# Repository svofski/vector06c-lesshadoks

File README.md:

ЛЕШАДОК ПОМПЕ
=============

ЛЕШАДОК ПОМПЕ (Les shadoks pompaient) is an expansion board for Вектор-06ц home computer from USSR era.

Features (real and planned):
  - [x] RAM disk expansion in SDRAM
  - [x] AY and other sound device emulation
  - [x] Joystick ports
  - [x] floppy disk emulator
  - [x] floppy images on SD card
  - [ ] floppy images downloaded from the internets
  - [x] ESP12F working as FPGA configurator
  - [x] ESP12F as user interface for SD card image selection
  - [ ] ESP12F for uploading floppy disk images to SDRAM
  - [ ] VI53 sound passthrough
  
Key hardware features:
  * Main chip: EP4CE6 Intel Cyclone IV device
  * 8MB SDRAM (working at 96MHz)
  * ESP12F module
  * Audio output with amplifier
  * Analog input for internal audio mixing (using LVDS sigma-delta ADC)

Board schematic
---------------
[Schematic](/kicad/shadok-cheap/shadok.pdf) (pdf)

Build instructions
------------------
This project consists of many parts and putting it together is not a simple task.
Here I wrote down some instructions primarily for myself to be able to remember
what to do. Good luck!

### PART 1 Building Cosmogol999 (esp8266 firmware)

1. Get the sources
```
git clone --recurse-submodules https://github.com/svofski/vector06c-lesshadoks
```

2. Prepare esp-open-sdk
Follow instructions at https://github.com/pfalcon/esp-open-sdk.
Mind the requirements, then get the SDK and build:
```
git clone --recursive --depth=1 https://github.com/pfalcon/esp-open-sdk.git
cd esp-open-sdk
make STANDALONE=y
```

After the toolchain is ready, do as it says:
```
export PATH=$HOME/esp-open-sdk/xtensa-lx106-elf/bin:$PATH
```
Also export SDK_BASE:
```
export SDK_BASE=$HOME/esp-open-sdk/ESP8266_NONOS_SDK-2.1.0-18-g61248df
```

3. Actually build

```
cd $HOME/vector06c-lesshadoks/esp8266/cosmogol999
make 
``` 

The firmware will be found in 
```
    rboot/firmware/rboot.bin
    firmware/shadki.bin
    blank_config.bin
```

6. Flash
```
make flash
```
This probably will do something destructive to your esp12f.

### PART 2 Building floppy emulator firmware

This one should be easy.
```
cd $HOME/vector06c-lesshadoks/6502
make
```

### PART 3 Building the FPGA programming files

1. Get and install Quartus Lite that supports Cyclone IV E (e.g. 17.1)

2. For the time being there is no makefile, so just open the project 
quartus/pompaient.qpf and press Ctrl-L.

### PART 4 Put it all together

???

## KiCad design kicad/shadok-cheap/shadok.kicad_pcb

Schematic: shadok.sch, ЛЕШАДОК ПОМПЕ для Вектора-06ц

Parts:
C101: 0.1; C_0603
J101, J103, J104: TEST_1P; WIREPAD_SMD_TINY
J105: SERIALS; Pin_Header_Straight_2x03
R101, R103: 100; R_0805
R102: 10K; R_0805
SW101: SW_Push; SW_SPST_FSMSM
U_101: EP4CE06E22; Altera_EQFP-144_20x20mm_Pitch0.5mm
X101: KXO-V97 50MHz; KXO-V97

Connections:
+1V2: U_101.5, U_101.29, U_101.37, U_101.45, U_101.61, U_101.78, U_101.102, U_101.109, U_101.116, U_101.134; also elsewhere on the board
+2V5: U_101.35, U_101.107; also elsewhere on the board
+3V3: C101.1, R102.2, U_101.17, U_101.26, U_101.40, U_101.47, U_101.56, U_101.62, U_101.81, U_101.93, U_101.117, U_101.122, U_101.130, U_101.139, X101.4; also elsewhere on the board
/ADC_SNDINT: U_101.87; also elsewhere on the board
/ADC_SNDn: U_101.98; also elsewhere on the board
/ADC_SNDp: U_101.99; also elsewhere on the board
/ASDO: U_101.6; also elsewhere on the board
/AUDIO_L: U_101.103; also elsewhere on the board
/AUDIO_R: U_101.101; also elsewhere on the board
/BUTT1: R102.1, SW101.1, U_101.25
/CONF_DONE: U_101.92; also elsewhere on the board
/DATA0: U_101.13; also elsewhere on the board
/DCLK/SPICLK: U_101.12, U_101.110; also elsewhere on the board
/ESP12F/RxD: J105.3; also elsewhere on the board
/ESP12F/TxD: J105.1; also elsewhere on the board
/ESP_RxD: R101.1, U_101.88
/ESP_TxD: R103.1, U_101.113
/FREE_IO2: J103.1, U_101.11
/MCLK: U_101.24, X101.3
/SDRAM_A0: U_101.76; also elsewhere on the board
/SDRAM_A1: U_101.77; also elsewhere on the board
/SDRAM_A2: U_101.80; also elsewhere on the board
/SDRAM_A3: U_101.83; also elsewhere on the board
/SDRAM_A4: U_101.71; also elsewhere on the board
/SDRAM_A5: U_101.70; also elsewhere on the board
/SDRAM_A6: U_101.69; also elsewhere on the board
/SDRAM_A7: U_101.68; also elsewhere on the board
/SDRAM_A8: U_101.67; also elsewhere on the board
/SDRAM_A9: U_101.66; also elsewhere on the board
/SDRAM_A10: U_101.75; also elsewhere on the board
/SDRAM_A11: U_101.65; also elsewhere on the board
/SDRAM_BA0: U_101.73; also elsewhere on the board
/SDRAM_BA1: U_101.74; also elsewhere on the board
/SDRAM_CKE: U_101.64; also elsewhere on the board
/SDRAM_CLK: U_101.60; also elsewhere on the board
/SDRAM_DLQM: U_101.42; also elsewhere on the board
/SDRAM_DQ0: U_101.28; also elsewhere on the board
/SDRAM_DQ1: U_101.30; also elsewhere on the board
/SDRAM_DQ2: U_101.31; also elsewhere on the board
/SDRAM_DQ3: U_101.32; also elsewhere on the board
/SDRAM_DQ4: U_101.33; also elsewhere on the board
/SDRAM_DQ5: U_101.34; also elsewhere on the board
/SDRAM_DQ6: U_101.38; also elsewhere on the board
/SDRAM_DQ7: U_101.39; also elsewhere on the board
/SDRAM_DQ8: U_101.58; also elsewhere on the board
/SDRAM_DQ9: U_101.55; also elsewhere on the board
/SDRAM_DQ10: U_101.54; also elsewhere on the board
/SDRAM_DQ11: U_101.53; also elsewhere on the board
/SDRAM_DQ12: U_101.52; also elsewhere on the board
/SDRAM_DQ13: U_101.51; also elsewhere on the board
/SDRAM_DQ14: U_101.50; also elsewhere on the board
/SDRAM_DQ15: U_101.49; also elsewhere on the board
/SDRAM_UDQM: U_101.59; also elsewhere on the board
/TCK: U_101.16; also elsewhere on the board
/TDI: U_101.15; also elsewhere on the board
/TDO: U_101.20; also elsewhere on the board
/TMS: U_101.18; also elsewhere on the board
/~CAS: U_101.105; also elsewhere on the board
/~CONFIG: U_101.14; also elsewhere on the board
/~CSO: U_101.8
/~DDIR: J101.1, U_101.10; also elsewhere on the board
/~ESP_SS: U_101.84; also elsewhere on the board
/~JOY_SS: U_101.111; also elsewhere on the board
/~RAS: U_101.106; also elsewhere on the board
/~SDRAM_CAS: U_101.44; also elsewhere on the board
/~SDRAM_CS: U_101.72; also elsewhere on the board
/~SDRAM_RAS: U_101.46; also elsewhere on the board
/~SDRAM_WE: U_101.43; also elsewhere on the board
/~SD_SS: U_101.112; also elsewhere on the board
/~STATUS: U_101.9; also elsewhere on the board
/~БЛК: U_101.100; also elsewhere on the board
/~ЗПВВ: U_101.89; also elsewhere on the board
/~ЗПЗУ: U_101.104; also elsewhere on the board
/~ЧТВВ: U_101.90; also elsewhere on the board
/~ЧТЗУ: U_101.91; also elsewhere on the board
/~ШАВВ0: U_101.3; also elsewhere on the board
/~ШАВВ1: U_101.2; also elsewhere on the board
/~ШАВВ2: U_101.1; also elsewhere on the board
/~ШАВВ3: U_101.144; also elsewhere on the board
/~ШАВВ4: U_101.143; also elsewhere on the board
/~ШАВВ5: U_101.142; also elsewhere on the board
/~ШАВВ6: U_101.141; also elsewhere on the board
/~ШАВВ7: U_101.138; also elsewhere on the board
/~ШАП0: U_101.137; also elsewhere on the board
/~ШАП1: U_101.136; also elsewhere on the board
/~ШАП2: U_101.135; also elsewhere on the board
/~ШАП3: U_101.133; also elsewhere on the board
/~ШАП4: U_101.132; also elsewhere on the board
/~ШАП5: U_101.129; also elsewhere on the board
/~ШАП6: U_101.128; also elsewhere on the board
/~ШАП7: U_101.127; also elsewhere on the board
/СБРОС: J104.1, U_101.23; also elsewhere on the board
/СТЕК: U_101.86; also elsewhere on the board
/СТРОБ_СОСТ: U_101.85; also elsewhere on the board
/ШД0: U_101.126; also elsewhere on the board
/ШД1: U_101.125; also elsewhere on the board
/ШД2: U_101.124; also elsewhere on the board
/ШД3: U_101.121; also elsewhere on the board
/ШД4: U_101.120; also elsewhere on the board
/ШД5: U_101.119; also elsewhere on the board
/ШД6: U_101.115; also elsewhere on the board
/ШД7: U_101.114; also elsewhere on the board
GND: C101.2, J105.5, J105.6, SW101.2, U_101.4, U_101.19, U_101.21, U_101.22, U_101.27, U_101.36, U_101.41, U_101.48, U_101.57, U_101.63, U_101.79, U_101.82, U_101.94, U_101.95, U_101.96, U_101.97, U_101.108, U_101.118, U_101.123, U_101.131, U_101.140, U_101.145, X101.2; also elsewhere on the board
unnamed: J105.2, R101.2
unnamed: J105.4, R103.2

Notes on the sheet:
MSEL=[0,1,0]: AS (EPCS4) 3.3V MSEL=[0,0,0]: PS (ESP12F) 3.3V
ASDO: Programming: EPCS4 via JTAG: Data Out User mode: Cyclone MISO DATA0: Cyclone configuration from ESP12F (input) User mode: Cyclone MOSI
EP4CE6 SRAM size: 2,944,088 bits
DCLK cannot be used as user output when in PS mode (Table 8-20) It is hard-tied with IO pin 110, which becomes output after CONFIG_DONE Programming (AS) 6 ASDO output 13 DATA0 input 12 DCLK output 8 nCSO output Programming (PS) 13 DATA0 input 12 DCLK input 14 nCONFIG input CONF_DONE output The dire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
BODGE IN REV1

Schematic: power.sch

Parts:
C201, C209, C210, C211, C212, C213, C214, C215, C216, C217, C218, C220, C221, C222, C223, C224, C225, C226, C227, C228, C229, C230, C231, C232: 0.1; C_0603
C202, C203, C204, C207: 4.7uF; C_0805
C205: 0.01uF; C_0603
C206, C208: 10uF; C_0805
L201, L202: L; R_1206
U201: ADP2108-1.2; TSOT-23-5
U202: LP2985-2.5; SOT-23-5
U203: ADP2108-3.3; TSOT-23-5

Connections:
+1V2: C201.1, C206.1, C209.1, C211.1, C214.1, C216.1, C221.1, C223.1, C224.1, C225.1, C228.1, L201.2, U201.4; also elsewhere on the board
+2V5: C207.1, C212.1, C217.1, U202.5 (VOUT); also elsewhere on the board
+3V3: C208.1, C210.1, C213.1, C215.1, C218.1, C220.1, C222.1, C226.1, C227.1, C229.1, C230.1, C231.1, C232.1, L202.2, U203.4; also elsewhere on the board
+5V: C202.1, C203.1, C204.1, U201.1, U201.3, U202.1 (VIN), U202.3 (ON/~OFF~), U203.1, U203.3; also elsewhere on the board
GND: C201.2, C202.2, C203.2, C204.2, C205.2, C206.2, C207.2, C208.2, C209.2, C210.2, C211.2, C212.2, C213.2, C214.2, C215.2, C216.2, C217.2, C218.2, C220.2, C221.2, C222.2, C223.2, C224.2, C225.2, C226.2, C227.2, C228.2, C229.2, C230.2, C231.2, C232.2, U201.2, U202.2 (GND), U203.2; also elsewhere on the board
unnamed: C205.1, U202.4 (BP)
unnamed: L201.1, U201.5
unnamed: L202.1, U203.5

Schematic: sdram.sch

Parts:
C301, C302, C303, C304, C306: 0.1; C_0603
C305: 22.0; CP_Tantalum_Case-B_EIA-3528-21_Reflow
U301: IS42S16400J; TSOP-2-54-0.8

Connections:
+3V3: C301.1, C302.1, C303.1, C304.1, C305.1, C306.1, U301.1, U301.3, U301.9, U301.14, U301.27, U301.43, U301.49; also elsewhere on the board
/SDRAM_A0: U301.23; also elsewhere on the board
/SDRAM_A1: U301.24; also elsewhere on the board
/SDRAM_A2: U301.25; also elsewhere on the board
/SDRAM_A3: U301.26; also elsewhere on the board
/SDRAM_A4: U301.29; also elsewhere on the board
/SDRAM_A5: U301.30; also elsewhere on the board
/SDRAM_A6: U301.31; also elsewhere on the board
/SDRAM_A7: U301.32; also elsewhere on the board
/SDRAM_A8: U301.33; also elsewhere on the board
/SDRAM_A9: U301.34; also elsewhere on the board
/SDRAM_A10: U301.22; also elsewhere on the board
/SDRAM_A11: U301.35; also elsewhere on the board
/SDRAM_BA0: U301.20; also elsewhere on the board
/SDRAM_BA1: U301.21; also elsewhere on the board
/SDRAM_CKE: U301.37; also elsewhere on the board
/SDRAM_CLK: U301.38; also elsewhere on the board
/SDRAM_DLQM: U301.15; also elsewhere on the board
/SDRAM_DQ0: U301.2; also elsewhere on the board
/SDRAM_DQ1: U301.4; also elsewhere on the board
/SDRAM_DQ2: U301.5; also elsewhere on the board
/SDRAM_DQ3: U301.7; also elsewhere on the board
/SDRAM_DQ4: U301.8; also elsewhere on the board
/SDRAM_DQ5: U301.10; also elsewhere on the board
/SDRAM_DQ6: U301.11; also elsewhere on the board
/SDRAM_DQ7: U301.13; also elsewhere on the board
/SDRAM_DQ8: U301.42; also elsewhere on the board
/SDRAM_DQ9: U301.44; also elsewhere on the board
/SDRAM_DQ10: U301.45; also elsewhere on the board
/SDRAM_DQ11: U301.47; also elsewhere on the board
/SDRAM_DQ12: U301.48; also elsewhere on the board
/SDRAM_DQ13: U301.50; also elsewhere on the board
/SDRAM_DQ14: U301.51; also elsewhere on the board
/SDRAM_DQ15: U301.53; also elsewhere on the board
/SDRAM_UDQM: U301.39; also elsewhere on the board
/~SDRAM_CAS: U301.17; also elsewhere on the board
/~SDRAM_CS: U301.19; also elsewhere on the board
/~SDRAM_RAS: U301.18; also elsewhere on the board
/~SDRAM_WE: U301.16; also elsewhere on the board
GND: C301.2, C302.2, C303.2, C304.2, C305.2, C306.2, U301.6, U301.12, U301.28, U301.41, U301.46, U301.52, U301.54; also elsewhere on the board

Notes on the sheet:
SDRAM

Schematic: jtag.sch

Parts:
J401: Conn_02x05_Odd_Even; IDC-Header_2x05_Pitch2.54mm_Straight
R401, R404, R406: 10K; R_0603
R403, R405, R407: 10K; R_0805
RN401: 25; R_Array_Concave_4x0603

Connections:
+2V5: J401.4, R403.2, R405.2; also elsewhere on the board
+3V3: R401.2, R404.2, R406.2; also elsewhere on the board
/CONF_DONE: R404.1; also elsewhere on the board
/TCK: RN401.1; also elsewhere on the board
/TDI: RN401.4; also elsewhere on the board
/TDO: RN401.2; also elsewhere on the board
/TMS: RN401.3; also elsewhere on the board
/~CONFIG: R401.1; also elsewhere on the board
/~STATUS: R406.1; also elsewhere on the board
GND: J401.2, J401.10, R407.1; also elsewhere on the board
unnamed: J401.1, R407.2, RN401.8
unnamed: J401.3, RN401.7
unnamed: J401.5, R405.1, RN401.6
unnamed: J401.9, R403.1, RN401.5

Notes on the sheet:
VCCIO of BANK0
Cyclone IV Handbook Figure 8-29 Programming Serial Configuration Devices In-System using the JTAG Interface
VCCA
These signals also to ESP12F

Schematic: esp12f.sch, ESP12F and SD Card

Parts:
C501: 220.0; CP_Tantalum_Case-D_EIA-7343-31_Reflow
C502: 0.1; C_0603
C503: 4.7; C_0805
J501: Micro_SD_Card; Conn_uSDcard
J502: TEST_1P; WIREPAD_SMD_TINY
JP501: SERIAL BUTTLOAD; Pin_Header_Straight_1x02
R501: 10K; R_0603
R502: 4K7; R_0603
R505: 10K; R_0805
RN501: 200; R_Array_Concave_4x0603
RN502: 3K3; R_Array_Concave_4x0603
U501: ESP12F; ESP-12E_SMD

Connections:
+3V3: C501.1, C502.1, C503.1, J501.4, R501.2, R505.1, RN502.7, RN502.8, U501.8; also elsewhere on the board
/ASDO: J501.7, RN501.2; also elsewhere on the board
/CONF_DONE: U501.14; also elsewhere on the board
/DATA0: J501.3, RN501.3; also elsewhere on the board
/DCLK/SPICLK: J501.5, RN501.1; also elsewhere on the board
/ESP12F/RxD: U501.15; also elsewhere on the board
/ESP12F/TxD: U501.16; also elsewhere on the board
/~CONFIG: U501.4; also elsewhere on the board
/~ESP_SS: R502.1, RN502.4, U501.10; also elsewhere on the board
/~SD_SS: J501.2, R505.2; also elsewhere on the board
GND: C501.2, C502.2, C503.2, J501.6, J501.9, JP501.2, R502.2, RN502.5, U501.9; also elsewhere on the board
unnamed: J502.1, R501.1, U501.1, U501.3
unnamed: JP501.1, RN502.1, U501.12
unnamed: RN501.6, U501.7
unnamed: RN501.7, U501.6
unnamed: RN501.8, U501.5
unnamed: RN502.2, U501.11

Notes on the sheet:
1. ESP12F is bus master after power on 2. ESP12F configures EP4CE06 using Passive Serial 3. EP4CE06 enters user mode 4. ESP12F becomes SPI slave with SS on IO9 5. SD Card is on the same bus, EP4CE06 is the master
IO16 has builtin pulldown others have pullus
10K pulldown on GPIO15 should be enough, but somehow it isn't. If RN502=10K, bodge R502 to enable boot.

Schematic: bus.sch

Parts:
C601, C602, C603, C604, C605, C606, C607, C608, C611: 0.1; C_0603
J601, J602, J603, J605: 74LVC8T245; TSSOP-24_4.4x7.8mm_Pitch0.65mm
J604: SNP34-90; СНП34С-90В-В(SNP34S)
Q601: BC817; SOT-23
R601, R602: 10K; R_0805
U601: 74LVC1T45; SOT-363_SC-70-6

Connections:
+3V3: C601.1, C603.1, C605.1, C607.1, C611.1, J601.1, J602.1, J603.23, J603.24, J605.1, R602.2, U601.6; also elsewhere on the board
+5V: C602.1, C604.1, C606.1, C608.1, J601.23, J601.24, J602.23, J602.24, J603.1, J604.2, J604.44, J604.47, J604.89, J605.23, J605.24, U601.1; also elsewhere on the board
/BUS/~CASЪ: J604.22, J604.69, J605.20
/BUS/~RASЪ: J604.21, J604.70, J605.21
/BUS/~БЛКЪ: J604.38, J604.53, U601.3
/BUS/~ВВОДЪ_СИСТЕМЫ: J604.39, J604.52, R601.2
/BUS/~ЗПВВЪ: J604.37, J604.54, J605.16
/BUS/~ЗПЗУЪ: J604.23, J604.68, J605.19
/BUS/~СБРОСЪ: J604.41
/BUS/~СБРЪ_СИСТЕМЫ: J604.55
/BUS/~ЧТВВЪ: J604.35, J604.56, J605.17
/BUS/~ЧТЗУЪ: J604.34, J604.57, J605.18
/BUS/СТЕКЪ: J604.40, J604.51, J605.15
/BUS/СТРОБЪ_СОСТЪ: J604.43, J604.48, J605.14
/BUS/ШДЪ0: J603.10, J604.25, J604.66
/BUS/ШДЪ1: J603.9, J604.26, J604.65
/BUS/ШДЪ2: J603.8, J604.27, J604.64
/BUS/ШДЪ3: J603.7, J604.28, J604.63
/BUS/ШДЪ4: J603.6, J604.29, J604.62
/BUS/ШДЪ5: J603.5, J604.30, J604.61
/BUS/ШДЪ6: J603.4, J604.31, J604.60
/BUS/ШДЪ7: J603.3, J604.32, J604.59
/~CAS: J605.4; also elsewhere on the board
/~DDIR: J603.2; also elsewhere on the board
/~RAS: J605.3; also elsewhere on the board
/~БЛК: U601.4; also elsewhere on the board
/~ЗПВВ: J605.8; also elsewhere on the board
/~ЗПЗУ: J605.5; also elsewhere on the board
/~ЧТВВ: J605.7; also elsewhere on the board
/~ЧТЗУ: J605.6; also elsewhere on the board
/~ШАВВ0: J601.3; also elsewhere on the board
/~ШАВВ1: J601.4; also elsewhere on the board
/~ШАВВ2: J601.5; also elsewhere on the board
/~ШАВВ3: J601.6; also elsewhere on the board
/~ШАВВ4: J601.7; also elsewhere on the board
/~ШАВВ5: J601.8; also elsewhere on the board
/~ШАВВ6: J601.9; also elsewhere on the board
/~ШАВВ7: J601.10; also elsewhere on the board
/~ШАП0: J602.3; also elsewhere on the board
/~ШАП1: J602.4; also elsewhere on the board
/~ШАП2: J602.5; also elsewhere on the board
/~ШАП3: J602.6; also elsewhere on the board
/~ШАП4: J602.7; also elsewhere on the board
/~ШАП5: J602.8; also elsewhere on the board
/~ШАП6: J602.9; also elsewhere on the board
/~ШАП7: J602.10; also elsewhere on the board
/СБРОС: Q601.3, R602.1; also elsewhere on the board
/СТЕК: J605.9; also elsewhere on the board
/СТРОБ_СОСТ: J605.10; also elsewhere on the board
/ШД0: J603.14; also elsewhere on the board
/ШД1: J603.15; also elsewhere on the board
/ШД2: J603.16; also elsewhere on the board
/ШД3: J603.17; also elsewhere on the board
/ШД4: J603.18; also elsewhere on the board
/ШД5: J603.19; also elsewhere on the board
/ШД6: J603.20; also elsewhere on the board
/ШД7: J603.21; also elsewhere on the board
GND: C601.2, C602.2, C603.2, C604.2, C605.2, C606.2, C607.2, C608.2, C611.2, J601.2, J601.11, J601.12, J601.13, J601.22, J602.2, J602.11, J602.12, J602.13, J602.22, J603.11, J603.12, J603.13, J603.22, J604.1, J604.11, J604.20, J604.24, J604.33, J604.45, J604.46, J604.58, J604.67, J604.71, J604.80, J604.90, J605.2, J605.11, J605.12, J605.13, J605.22, Q601.2, U601.2, U601.5; also elsewhere on the board
unnamed: J601.14, J604.10, J604.81
unnamed: J601.15, J604.9, J604.82
unnamed: J601.16, J604.8, J604.83
unnamed: J601.17, J604.7, J604.84
unnamed: J601.18, J604.6, J604.85
unnamed: J601.19, J604.5, J604.86
unnamed: J601.20, J604.4, J604.87
unnamed: J601.21, J604.3, J604.88
unnamed: J602.14, J604.19, J604.72
unnamed: J602.15, J604.18, J604.73
unnamed: J602.16, J604.17, J604.74
unnamed: J602.17, J604.16, J604.75
unnamed: J602.18, J604.15, J604.76
unnamed: J602.19, J604.14, J604.77
unnamed: J602.20, J604.13, J604.78
unnamed: J602.21, J604.12, J604.79
unnamed: Q601.1, R601.1

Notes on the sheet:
Шинные приемопередатчики
BODGE IN REV 1

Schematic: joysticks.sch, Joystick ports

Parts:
J701, J702: DB9_Male_MountingHoles; DSUB-9_Male_Vertical_Pitch2.77x2.84mm
R701: 10K; R_0805
RN701, RN702, RN705, RN706: 10K; R_Array_Concave_4x0603
U701: MCP23S17; SSOP-28_5.3x10.2mm_Pitch0.65mm

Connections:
+3V3: RN701.1, RN701.2, RN701.3, RN701.4, RN702.1, RN702.2, RN702.3, RN702.4, RN705.1, RN705.2, RN705.3, RN705.4, RN706.1, RN706.2, RN706.3, RN706.4, U701.9, U701.18; also elsewhere on the board
/ASDO: U701.14; also elsewhere on the board
/DATA0: U701.13; also elsewhere on the board
/DCLK/SPICLK: U701.12; also elsewhere on the board
/Joysticks/~P1B1: J702.6, RN706.7, U701.4
/Joysticks/~P1B2: J702.9, RN705.6, U701.3
/Joysticks/~P1B3: J702.5, RN705.5, U701.2
/Joysticks/~P1B4: J702.7, RN706.5, U701.1
/Joysticks/~P1DN: J702.2, RN706.6, U701.7
/Joysticks/~P1LT: J702.3, RN705.8, U701.6
/Joysticks/~P1RT: J702.4, RN705.7, U701.5
/Joysticks/~P1UP: J702.1, RN706.8, U701.8
/Joysticks/~P2B1: J701.6, RN702.7, U701.24
/Joysticks/~P2B2: J701.9, RN701.6, U701.23
/Joysticks/~P2B3: J701.5, RN701.5, U701.22
/Joysticks/~P2B4: J701.7, RN702.5, U701.21
/Joysticks/~P2DN: J701.2, RN702.6, U701.27
/Joysticks/~P2LT: J701.3, RN701.8, U701.26
/Joysticks/~P2RT: J701.4, RN701.7, U701.25
/Joysticks/~P2UP: J701.1, RN702.8, U701.28
/~JOY_SS: R701.1, U701.11; also elsewhere on the board
GND: J701.8, J702.8, U701.10, U701.15, U701.16, U701.17; also elsewhere on the board

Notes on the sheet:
BODGE in Rev.1 (was GND)

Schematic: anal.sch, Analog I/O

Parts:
C801: 10.0; CP_Tantalum_Case-B_EIA-3528-21_Reflow
C803: 0.01; C_0603
C805, C815, C817: 0.1; C_0603
C807, C808: 1000; C_0805
C809, C810, C813: 1.0; C_0805
C820, C822: 47.0; CP_Tantalum_Case-B_EIA-3528-21_Reflow
C821: 47.0; CP_Tantalum_Case-D_EIA-7343-31_Reflow
D801: BAT54S; SOT-23
J801: Conn_01x02; Socket_Strip_Angled_2x01
J815: Audio Out; ST-215N-04
L801: BLM21AG102SN1D; R_0805
R802: 470; R_0805
R804, R805: 5K; R_0805
R808, R809, R811, R814: 15K; R_0805
RV801: 100K; Potentiometer_Bourns_3296W_3-8Zoll_Inline_ScrewUp
U801: TPA6110A2; MSOP-8-1EP_3x3mm_Pitch0.65mm

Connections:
+2V5: C805.2, D801.2, RV801.1; also elsewhere on the board
+5V: C815.2, C821.1, L801.1; also elsewhere on the board
/ADC_SNDINT: R802.2; also elsewhere on the board
/ADC_SNDn: C803.2, R802.1; also elsewhere on the board
/ADC_SNDp: C801.2, D801.3, RV801.2; also elsewhere on the board
/AUDIO_L: R804.2; also elsewhere on the board
/AUDIO_R: R805.2; also elsewhere on the board
/anal/POWERPAD: U801.9
/anal/V06C_AUDIO: C801.1, J801.2
GND: C803.1, C805.1, C807.1, C808.1, C813.1, C815.1, C817.1, C821.2, D801.1, J801.1, J815.3, RV801.3, U801.2, U801.3; also elsewhere on the board
unnamed: C807.2, C810.2, R805.1
unnamed: C808.2, C809.2, R804.1
unnamed: C809.1, R808.2
unnamed: C810.1, R809.2
unnamed: C813.2, U801.1
unnamed: C817.2, L801.2, U801.6
unnamed: C820.1, R814.2, U801.7
unnamed: C820.2, J815.2
unnamed: C822.1, R811.2, U801.5
unnamed: C822.2, J815.1
unnamed: R808.1, R814.1, U801.8
unnamed: R809.1, R811.1, U801.4

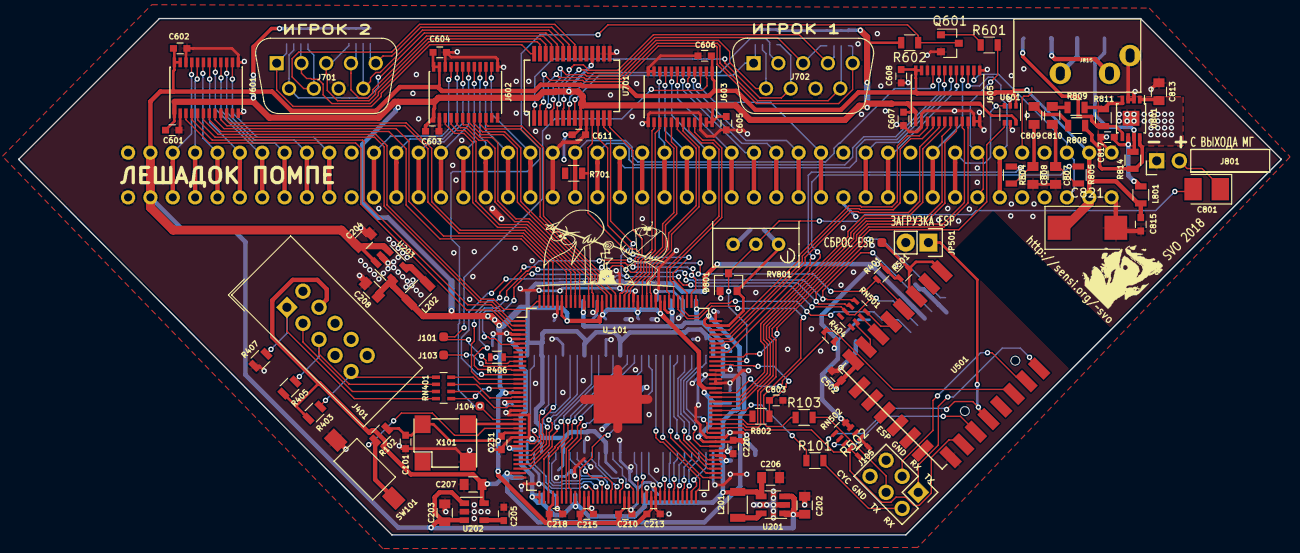
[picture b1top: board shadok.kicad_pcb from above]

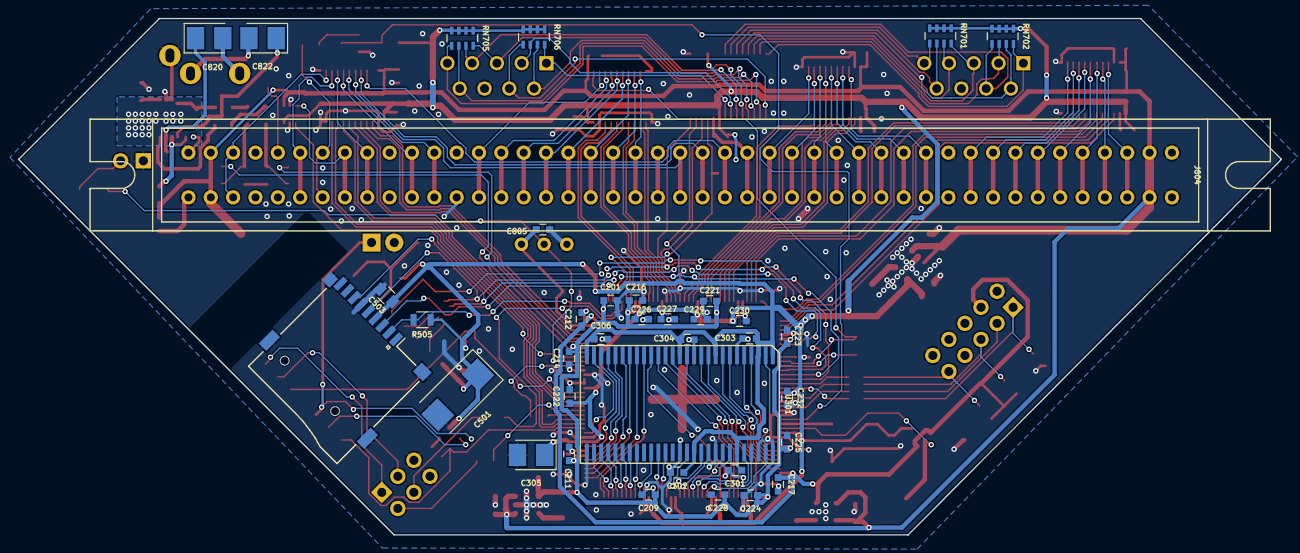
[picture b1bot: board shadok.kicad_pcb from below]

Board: 2 copper layers, 141.2 x 57.8 mm, 126 parts (37 on the bottom side), 182 nets.

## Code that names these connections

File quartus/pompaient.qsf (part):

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#set_instance_assignment -name IO_STANDARD LVDS -to ADC_SND
#set_location_assignment PIN_98 -to "ADC_SND(n)"
#set_location_assignment PIN_99 -to ADC_SND
#set_location_assignment PIN_87 -to ADC_SNDINT
set_location_assignment PIN_110 -to SPI_CLK
set_location_assignment PIN_13 -to SPI_MOSI
set_location_assignment PIN_6 -to SPI_MISO
set_location_assignment PIN_25 -to BUTT1
set_location_assignment PIN_84 -to ESP_SS_N
set_location_assignment PIN_88 -to ESP_RXD
set_location_assignment PIN_113 -to ESP_TXD
set_location_assignment PIN_112 -to SD_SS_N
set_location_assignment PIN_111 -to JOY_SS_N
set_location_assignment PIN_3 -to VU_SHAVV_N[0]
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set_location_assignment PIN_85 -to VU_STROB_SOST
set_location_assignment PIN_99 -to ADC_SND
set_location_assignment PIN_98 -to "ADC_SND(n)"
set_location_assignment PIN_87 -to ADC_SNDINT
set_global_assignment -name PARTITION_NETLIST_TYPE SOURCE -section_id Top
set_global_assignment -name PARTITION_FITTER_PRESERVATION_LEVEL PLACEMENT_AND_ROUTING -section_id Top
set_global_assignment -name PARTITION_COLOR 16764057 -section_id Top
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set_instance_assignment -name FAST_OUTPUT_REGISTER ON -to DRAM_BA_0
set_instance_assignment -name FAST_OUTPUT_REGISTER ON -to DRAM_BA_1
set_instance_assignment -name AUTO_GLOBAL_CLOCK ON -to DRAM_CLK
set_location_assignment PIN_11 -to FREE_IO2
set_instance_assignment -name WEAK_PULL_UP_RESISTOR ON -to FREE_IO2
set_location_assignment PIN_101 -to AUDIO_R
set_location_assignment PIN_103 -to AUDIO_L
set_instance_assignment -name IO_STANDARD "2.5 V" -to AUDIO_L
set_instance_assignment -name IO_STANDARD "2.5 V" -to AUDIO_R
set_instance_assignment -name IO_MAXIMUM_TOGGLE_RATE "0 MHz" -to AUDIO_L
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
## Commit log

2018-03-09 frist commut
2018-03-09 fixed the fuckups from the first version
    had to remove video module
2018-03-13 version 2 with all the required signals
2018-07-08 rascas
2018-07-08 waveforms
2018-07-08 waveforms code screenshot
2018-07-08 rascas fixes
2018-07-10 merde
2018-07-16 first working version
    kvaz in sdram
    AY emulation
2018-07-16 schematic sheet update + pdf
2018-07-16 photo
2018-07-17 fixed reset debounce
    it was held for too long, so first commands programming kvaz were likely to be
    ignored
2018-07-17 sdram arbitre for zpu or anything really WIP
2018-07-20 updated schematics
    reset bodge documented
2018-07-23 initial version of esp8266 firmware
    * implemented basic file manager for configuration files
    * files can be uploaded, deleted, selected for boot
2018-07-24 140medley.min.js in the root
2018-07-25 ota upgrade with rboot + fpga config
2018-07-25 build id
2018-07-25 libesphttpd moved in because differences
2018-07-25 attempt to fix captive portal
2018-07-26 fine, but impossible to reduce tx power
    esp-open-rtos does not provide system_phy_set_max_tpw(), which makes it
    impossible to reduce output power and interference on v06c display
2018-07-29 esp-open-sdk version
    * seems to build, work, ota-update, spiffs-file-upload just fine
    * exhibits strange forgetfulness of wifi settings after power down
    * was hard to build but has much less mysteries that the esp-open-rtos
    version
    * actual fpga configuration in the borat not yet tested
2018-07-29 noos sdk works
    no interference when sleep is disabled
2018-07-31 simulated floppy, sdram arbitre
2018-07-31 floppysrc from v06cc
2018-07-31 switched cc65 to vector06cc branch
2018-07-31 paths
2018-08-01 documented bodge pulldown R502 across RN502
2018-08-01 FUCK GIT
2018-08-01 added rboot as local files, not submodule
    because fuck git
2018-08-01 firmwares
2018-08-03 +floppy +arbitre
    * kdtest still passes ok
    * floppy mounts sd card, but does not talk to the host
2018-08-04 reads data but problem with status or seek
    signaltap verified that the data are correct.
    seek parameters HST appear to mismatch though:
    track looks correct (beginning of directory)
    head seems ok (starting with 1)
    sector begins ok but then fails to advance.
    MDOS reports
2018-08-07 bloody black ice loads!!!!!
2018-08-09 floppy can access sdram window
2018-08-11 spi slave wip
2018-08-18 move heatshrink to flash
2018-08-18 disk image selector works with a dummy arduino soc
2018-08-18 floppy 6502 before work on fdd selector via web
2018-08-18 support esp12f file catalog and selection
2018-08-18 cont..
2018-08-21 web interface for floppy selection works, kinda
    The only excuse for this shitty commit is to get a working demo for CC'2018.
    * a bit more robust state handling in the esp8266
    * timeouts on both sides, so that nothing lingers forever hopefully
    * delayed spi slave initialisation seems to help with reboots on bootup
    * floppy/spi.v works at 24MHz for sd card, at 12MHz for ESP12F
    Checking this in because there's no time to make it better. In the
2018-08-21 verilog parts supplementing the last commit
2018-08-22 wip fakerom
2018-08-23 working fake bootrom!
2018-08-23 added emulated 8253
2018-08-23 working fakeboot
2018-08-23 sense VU_VVOD as sys_reset
2018-09-01 wip on joysticks: compiles, not tested
    - polling joysticks in the code
    - hopefully 12mhz is okay with mcp23s17 (nominally 10mhz max)
    - route all input signals form p1/p2 to ports $0e, $0f
2018-09-03 joystick "C" on ports 2e/2f works well
2018-09-03 uspid joystick on port 27
2018-09-06 wip: rom selector, fdd A/B... NOT WORKING YET
    * inifile in ESP12F for persisting selections, modes, etc
    * SoC requests initial images, modes from ESP12F at boot
    * new SD-card directory structure:
    /V06C/FDD
    /V06C/EDD
    /V06C/ROM
2018-09-07 pages in ui, mostly. wip
2018-09-10 modal catalogs html/esp/soc
    mode is stored in the inifile
    user page makes catalog request, specifying mode
    esp converts mode string into code and passes on to SoC, gets response
2019-06-29 Added Arlet's 6502 with clken
    Base commit a11631082b20e8a0746cd5cc4ae8bbe68bff79c4
2019-06-29 build instructions and some makefile fixes

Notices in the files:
quartus/pompaient.qsf:
Copyright (C) 2017  Intel Corporation. All rights reserved.
